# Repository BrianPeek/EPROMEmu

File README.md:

# EPROMEmu

**!! WARNING: I have no idea what I'm doing !!**

I've decided to make this public in the rare event it might help someone.

This is a very simple, likely very wrong (EP)ROM emulator using a Teensy 4.1 and Arduino/PlatformIO.  It works for my purposes (emulating an EPROM for
use in an Atari Lynx EPROM cartridge), but it it is probably not the "correct" way to design hardware.  I have also used it on Game Gear and Vectrex EPROM cartridges,
but it was not heavily tested.

Please take caution with using anything you see here.  It's my first time using KiCad, my first time designing a PCB, and my first time creating hardware.  Again,
it works for my purposes, but perhaps it'll burn your house down.

Enjoy!

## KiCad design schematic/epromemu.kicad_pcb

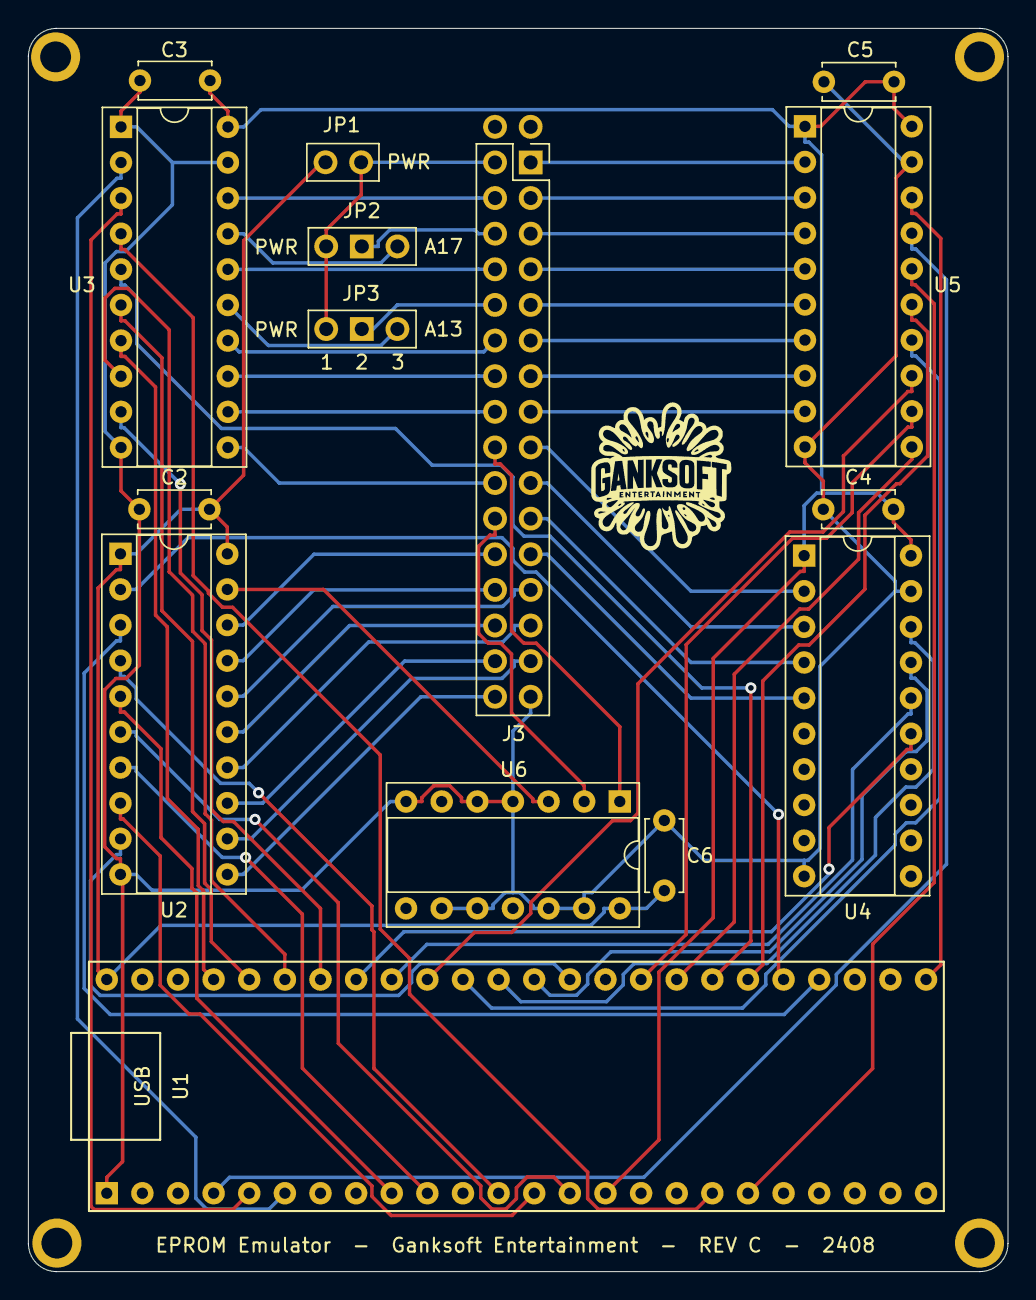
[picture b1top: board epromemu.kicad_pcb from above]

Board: 2 copper layers, 69.9 x 88.6 mm, 20 parts (0 on the bottom side), 65 nets.

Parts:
C2, C3, C4, C5, C6: 0.1uf; C_Disc_D5.0mm_W2.5mm_P5.00mm
GanksoftLogo: LOGO; GanksoftLogo
H1, H2, H3, H4: MountingHole; MountingHole_2.2mm_M2_ISO7380_Pad
J3: EPROM Connector; PinHeader_2x16_P2.54mm_Vertical
JP1: PWR; PinHeader_1x02_P2.54mm_Vertical
JP2: A17; PinHeader_1x03_P2.54mm_Vertical
JP3: A13; PinHeader_1x03_P2.54mm_Vertical
U1: Teensy4.1; Teensy41
U2, U3, U4, U5: 74HC245; DIP-20_W7.62mm_Socket
U6: 74HC32; DIP-14_W7.62mm_Socket

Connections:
+3V3: C3.1, C4.1, C5.1, U1.15 (3V3), U3.20 (VCC), U4.1 (A->B), U4.20 (VCC), U5.1 (A->B), U5.20 (VCC)
+5V: C2.1, C6.1, JP1.2 (B), U1.48 (VIN), U2.1 (A->B), U2.20 (VCC), U6.14 (VCC)
A0_3V3: U1.41 (19_A5_SCL), U4.15 (B3)
A0_5V: J3.12, U4.5 (A3)
A1_3V3: U1.40 (18_A4_SDA), U4.16 (B2)
A1_5V: J3.11, U4.4 (A2)
A2_3V3: U1.36 (14_A0_TX3_SPDIF_OUT), U4.17 (B1)
A2_5V: J3.10, U4.3 (A1)
A3_3V3: U1.37 (15_A1_RX3_SPDIF_IN), U4.18 (B0)
A3_5V: J3.9, U4.2 (A0)
A4_3V3: U1.32 (40_A16), U5.11 (B7)
A4_5V: J3.8, U5.9 (A7)
A5_3V3: U1.33 (41_A17), U5.12 (B6)
A5_5V: J3.7, U5.8 (A6)
A6_3V3: U1.39 (17_A3_TX4_SDA1), U5.13 (B5)
A6_5V: J3.6, U5.7 (A5)
A7_3V3: U1.38 (16_A2_RX4_SCL1), U5.14 (B4)
A7_5V: J3.5, U5.6 (A4)
A8_3V3: U1.44 (22_A8_CTX1), U3.6 (A4)
A8_5V: J3.27, U3.14 (B4)
A9_3V3: U1.45 (23_A9_CRX1_MCLK1), U3.7 (A5)
A9_5V: J3.26, U3.13 (B5)
A10_3V3: U1.42 (20_A6_TX5_LRCLK1), U3.9 (A7)
A10_5V: J3.23, U3.11 (B7)
A11_3V3: U1.43 (21_A7_RX5_BCLK1), U3.8 (A6)
A11_5V: J3.25, U3.12 (B6)
A12_3V3: U1.30 (38_CS1_IN1), U5.15 (B3)
A12_5V: J3.4, U5.5 (A3)
A13_3V3: U1.31 (39_MISO1_OUT1A), U3.5 (A3)
A13_5V: JP3.3 (B), U3.15 (B3)
A14_3V3: U1.18 (26_A12_MOSI1), U3.4 (A2)
A14_5V: J3.29, U3.16 (B2)
A15_3V3: U1.19 (27_A13_SCK1), U5.16 (B2)
A15_5V: J3.3, U5.4 (A2)
A16_3V3: U1.4 (2_OUT2), U5.17 (B1)
A16_5V: J3.2, U5.3 (A1)
A17_3V3: U1.5 (3_LRCLK2), U3.3 (A1)
A17_5V: JP2.3 (B), U3.17 (B1)
A18_3V3: U1.6 (4_BCLK2), U3.2 (A0)
A18_5V: J3.31, U3.18 (B0)
A19_3V3: U1.25 (33_MCLK2), U5.18 (B0)
A19_5V: J3.1, U5.2 (A0)
CE_5V: J3.22, U6.2
D0_3V3: U1.12 (10_CS_MQSR), U2.4 (A2)
D0_5V: J3.13, U2.16 (B2)
D1_3V3: U1.14 (12_MISO_MQSL), U2.6 (A4)
D1_5V: J3.14, U2.14 (B4)
D2_3V3: U1.13 (11_MOSI_CTX1), U2.8 (A6)
D2_5V: J3.15, U2.12 (B6)
D3_3V3: U1.35 (13_SCK_LED), U2.9 (A7)
D3_5V: J3.17, U2.11 (B7)
D4_3V3: U1.10 (8_TX2_IN1), U2.7 (A5)
D4_5V: J3.18, U2.13 (B5)
D5_3V3: U1.9 (7_RX2_OUT1A), U2.5 (A3)
D5_5V: J3.19, U2.15 (B3)
D6_3V3: U1.28 (36_CS), U2.3 (A1)
D6_5V: J3.20, U2.17 (B1)
D7_3V3: U1.29 (37_CS), U2.2 (A0)
D7_5V: J3.21, U2.18 (B0)
GND: C2.2, C3.2, C4.2, C5.2, C6.2, J3.16, U1.1 (GND), U2.10 (GND), U3.1 (A->B), U3.10 (GND), U3.19 (CE), U4.10 (GND), U4.19 (CE), U5.10 (GND), U5.19 (CE), U6.4, U6.5, U6.7 (GND), U6.9, U6.10, U6.12, U6.13
JP1_PWR: J3.32, JP1.1 (A), JP2.1 (A), JP3.1 (A)
unnamed: J3.28, JP3.2 (C)
unnamed: J3.30, JP2.2 (C)
unnamed: U2.19 (CE), U6.3
OE_5V: J3.24, U6.1

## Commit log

2021-12-11 v1 of board, about to change it...
2021-12-11 update gitignore
2021-12-11 remove ignored files
2021-12-24 updates'
2021-12-26 final?
2021-12-27 submitted v0.1
2021-12-28 update code
2021-12-29 update to v6
2022-01-01 it kinda works!
2022-01-02 v0.2 updates
2022-01-03 v0.2 in progress...
2022-01-03 1mbit fixes, tweaks
2022-01-05 tweaks
2022-06-27 v2 updates
2022-07-06 v2 changes (no more ce/pgm pins)
2022-07-10 2 serial modes + SD card
2022-07-16 starting v0.3
2022-09-14 removed unused dirs
2022-09-14 remove test dir
2022-09-15 remove bin files
2022-09-15 update ignore
2022-09-28 start of different EPROM sizes
2022-09-28 oops
2022-09-28 update ignore/extensions
2022-09-28 update firmware + sender
2022-09-28 remove unknown, always default to 2mbit
2022-10-01 Oops, needs FullName, not Name
2022-10-20 add pdf schematic
2022-10-21 remove unused files
2022-12-22 add skip option
2022-12-24 remove mirror copy
2023-05-21 add 1mbit support
2023-09-08 base mode on size of rom on disk
2024-07-20 a complete v3?
2024-07-26 mounting holes
2024-08-05 Rev C schem/pcb
2024-08-05 remove lck
2024-08-06 remove old schematic, it's in git history
2025-11-27 change default to COM4
